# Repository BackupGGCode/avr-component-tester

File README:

The firmware was specificly designed to on an Atmega328p but really; 
any 28pin atmega 8k and up will work; and as long as your utilizing 
winavr just make sure you include its IO header file; you should be 
able to upload the source no problem. Ensure to double check the 
pinout and make changes as needed.

At some point I will most likly include differnt pre-compiled files 
for multiple atmega's for the public, depending on if there is any 
demand at all. Most likly there will be none, as its really just a 
personal project.

I also have some left-over PCBs; so if your interested just contact
BrentBXR and I might be able to mail you one. As long as you promise 
to build it up, and enjoy it. I wont send somone a PCB just so they 
can have a PCB laying around...

Thanks -BrentBXR [@gmail]

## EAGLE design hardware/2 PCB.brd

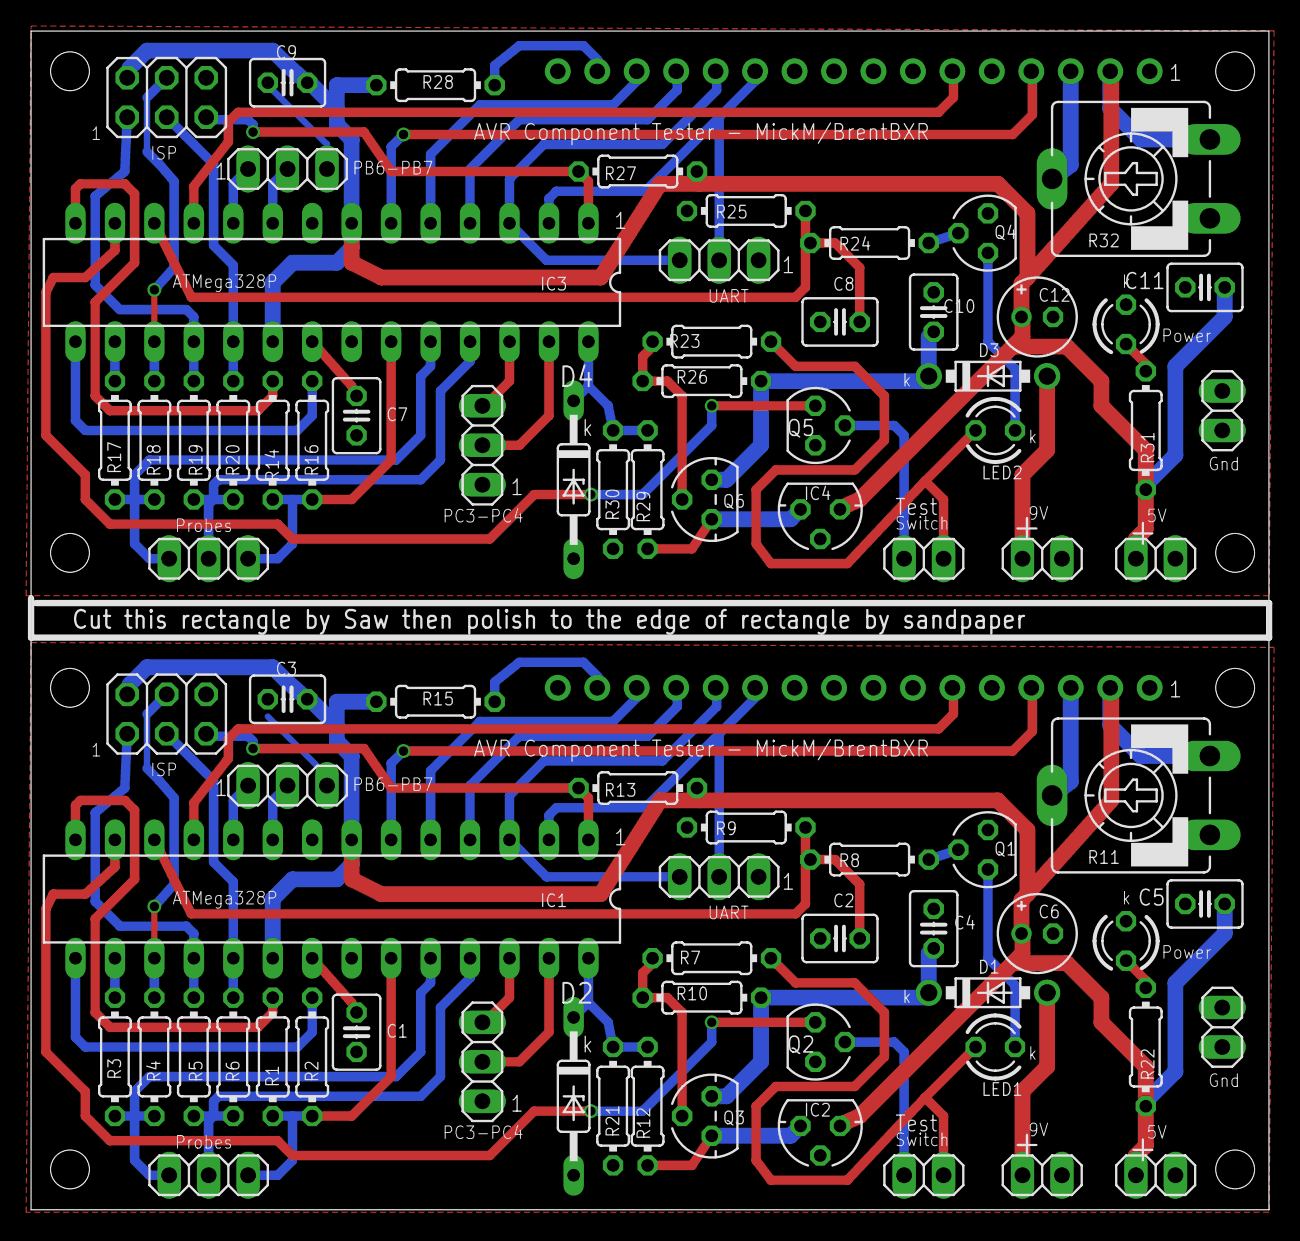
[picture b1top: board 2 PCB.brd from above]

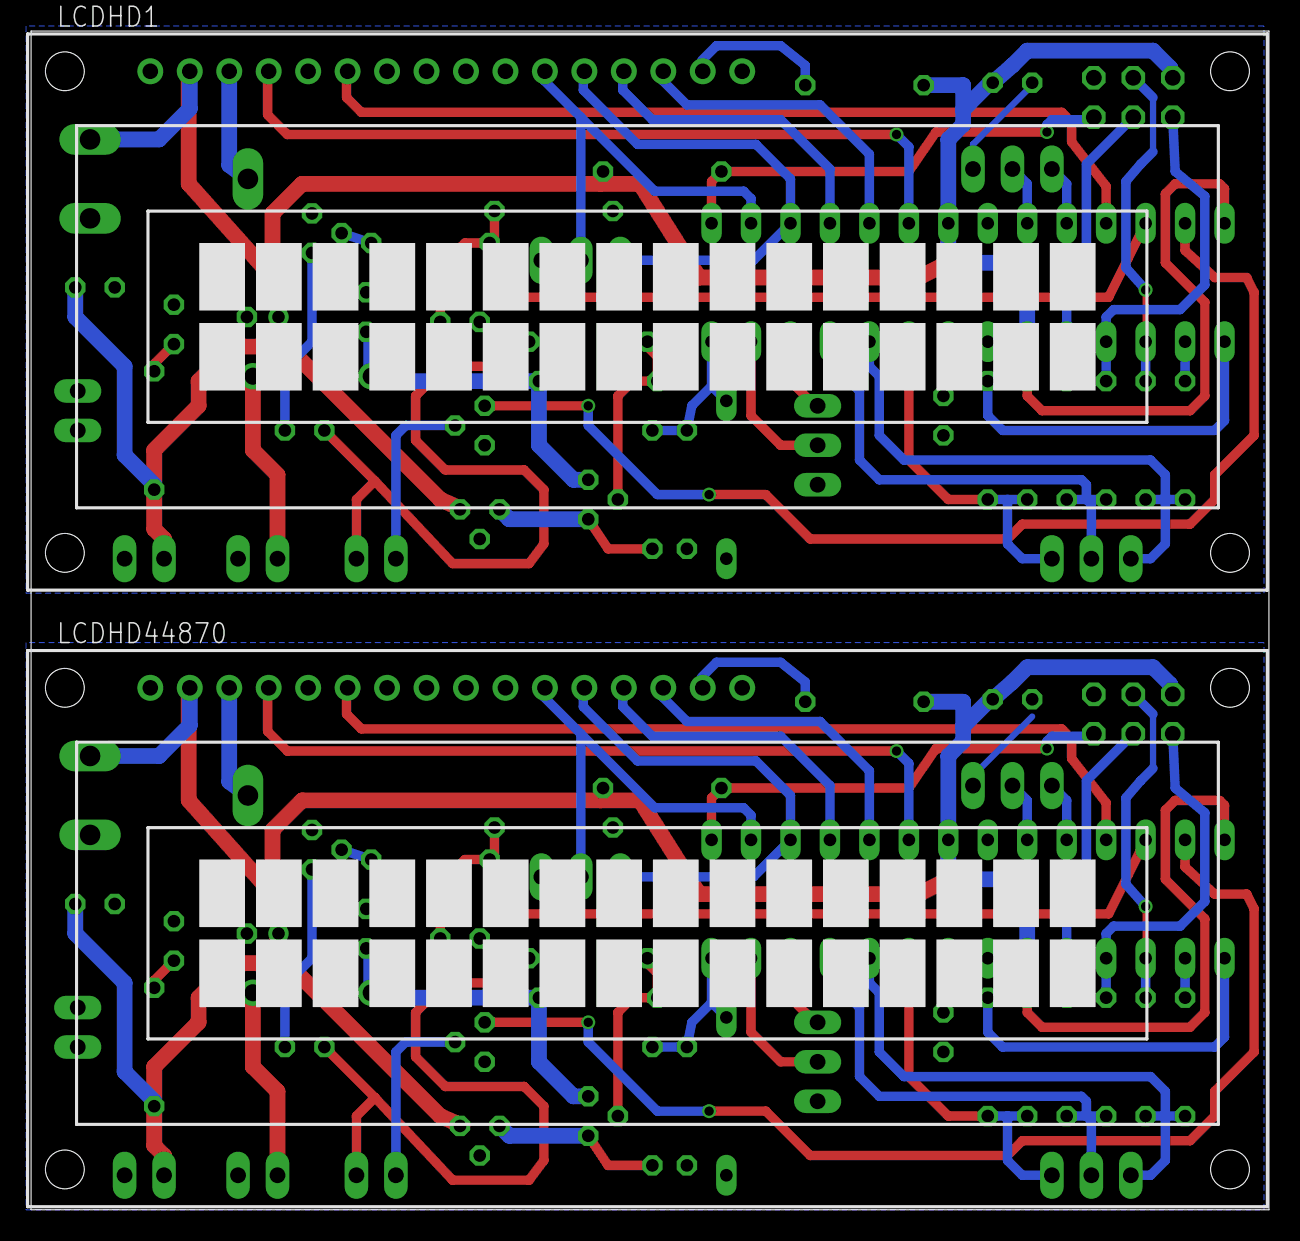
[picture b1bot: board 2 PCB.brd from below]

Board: 2 copper layers, 79.7 x 75.9 mm, 82 parts (2 on the bottom side), 74 nets.

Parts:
9V-DC-IN, 9V-DC-IN1: 1X02
C1, C3, C4, C5, C7, C9, C10, C11: 100n; C025-030X050
C2, C8: 100nF; C025-030X050
C6, C12: 100uF; E2-5
D1, D3: 1N5817-B; DO41-7.6
D2, D4: 5V1; DO35Z10
GND, GND1: 1X02
IC1, IC3: MEGA8-P; DIL28-3
IC2, IC4: 7805L; 78LXX
ISP, ISP1: 2X03
LCDHD1, LCDHD44870: TUXGR_16X2_R2
LED1, LED2: LED; LED3MM
PB6-PB1, PB6-PB7: 1X03
PC3-PC1, PC3-PC4: 1X03
PROBES, PROBES1: 1X03
PWR, PWR1: LED; LED3MM
Q1, Q2, Q4, Q5: BC547; SOT54A
Q3, Q6: BC557; TO92
R1, R3, R5, R14, R17, R19: 750R; 0204/7
R2, R4, R6, R16, R18, R20: 500K; 0204/7
R7, R23: 27k; 0204/7
R8, R24: 27K; 0204/7
R9, R25: 100K; 0204/7
R10, R26: 33K; 0204/7
R11, R32: 10K; CA9V
R12, R13, R27, R29: 10K; 0204/7
R15, R28: 150R; 0204/7
R21, R30: 3K3; 0204/7
R22, R31: 680R; 0204/7
TEST-SWITCH, TEST-SWITCH1: 1X02
UART, UART1: 1X03
VCC-GND, VCC-GND1: 1X02

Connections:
+5V: C3.1, C5.1, C6.+, IC1.7, IC1.20, IC2.OUT, ISP.2, LCDHD44870.2, R11.E, R13.1, R15.2, R22.1, VCC-GND.1
+5V1: C9.1, C11.1, C12.+, IC3.7, IC3.20, IC4.OUT, ISP1.2, LCDHD1.2, R27.1, R28.2, R31.1, R32.E, VCC-GND1.1
BAT-MON: D2.C, IC1.28, R12.2, R21.1
BAT-MON1: D4.C, IC3.28, R29.2, R30.1
GND: 9V-DC-IN.2, C1.2, C2.2, C3.2, C4.2, C5.2, C6.-, D2.A, GND.1, GND.2, IC1.8, IC1.22, IC2.GND, ISP.6, LCDHD44870.1, LCDHD44870.5, LCDHD44870.16, PB6-PB7.3, PC3-PC4.1, PWR.K, Q1.E, Q2.E, R9.1, R11.A, R21.2, UART.1, VCC-GND.2
GND1: 9V-DC-IN1.2, C7.2, C8.2, C9.2, C10.2, C11.2, C12.-, D4.A, GND1.1, GND1.2, IC3.8, IC3.22, IC4.GND, ISP1.6, LCDHD1.1, LCDHD1.5, LCDHD1.16, PB6-PB1.3, PC3-PC1.1, PWR1.K, Q4.E, Q5.E, R25.1, R30.2, R32.A, UART1.1, VCC-GND1.2
MISO: IC1.18, ISP.1, R5.1
MISO1: IC3.18, ISP1.1, R19.1
MOSI: IC1.17, ISP.4, R4.1
MOSI1: IC3.17, ISP1.4, R18.1
unnamed: IC2.IN, Q3.3, R12.1
unnamed: 9V-DC-IN.1, D1.A
unnamed: IC1.23, PROBES.3, R1.2, R2.2
unnamed: IC1.13, Q2.C
unnamed: IC1.25, PROBES.2, R5.2, R6.2
unnamed: IC1.14, R1.1
unnamed: IC1.15, R2.1
unnamed: IC1.16, R3.1
unnamed: PWR.A, R22.2
unnamed: IC3.23, PROBES1.3, R14.2, R16.2
unnamed: IC3.14, R14.1
unnamed: Q3.2, R7.2, R10.1
unnamed: IC1.6, LCDHD44870.4
unnamed: IC3.15, R16.1
unnamed: IC1.24, PROBES.1, R3.2, R4.2
unnamed: Q1.B, R8.2
unnamed: IC3.16, R17.1
unnamed: IC3.24, PROBES1.1, R17.2, R18.2
unnamed: IC1.9, PB6-PB7.2
unnamed: LED1.A, R7.1, TEST-SWITCH.2
unnamed: LED1.K, Q1.C
unnamed: Q2.B, TEST-SWITCH.1
unnamed: C2.1, IC1.12, R8.1, R9.2
unnamed: IC1.11, LCDHD44870.6
unnamed: Q6.2, R23.2, R26.1
unnamed: IC1.4, LCDHD44870.13
unnamed: IC1.5, LCDHD44870.14
unnamed: LCDHD44870.3, R11.S
unnamed: C1.1, IC1.21
unnamed: IC1.10, PB6-PB7.1
unnamed: LCDHD44870.15, R15.1
unnamed: Q4.B, R24.2
unnamed: C4.1, D1.C, Q3.1, R10.2
unnamed: IC1.26, PC3-PC4.3
unnamed: LED2.A, R23.1, TEST-SWITCH1.2
unnamed: LED2.K, Q4.C
unnamed: IC1.27, PC3-PC4.2
unnamed: Q5.B, TEST-SWITCH1.1
unnamed: IC3.6, LCDHD1.4
unnamed: IC3.4, LCDHD1.13
unnamed: IC3.5, LCDHD1.14
unnamed: IC3.11, LCDHD1.6
unnamed: LCDHD1.15, R28.1
unnamed: C10.1, D3.C, Q6.1, R26.2
unnamed: LCDHD1.3, R32.S
unnamed: 9V-DC-IN1.1, D3.A
unnamed: C7.1, IC3.21
unnamed: C8.1, IC3.12, R24.1, R25.2
unnamed: IC4.IN, Q6.3, R29.1
unnamed: IC3.26, PC3-PC1.3
unnamed: IC3.27, PC3-PC1.2
unnamed: IC3.9, PB6-PB1.2
unnamed: IC3.10, PB6-PB1.1
unnamed: IC3.25, PROBES1.2, R19.2, R20.2
unnamed: PWR1.A, R31.2
unnamed: IC3.13, Q5.C
RST: IC1.1, ISP.5, R13.2
RST1: IC3.1, ISP1.5, R27.2
RXD: IC1.2, LCDHD44870.11, UART.2
RXD1: IC3.2, LCDHD1.11, UART1.2
SCK: IC1.19, ISP.3, R6.1
SCK1: IC3.19, ISP1.3, R20.1
TXD: IC1.3, LCDHD44870.12, UART.3
TXD1: IC3.3, LCDHD1.12, UART1.3

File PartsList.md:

&lt;BR&gt;

Edited partlist exported from Eagle


&lt;BR&gt;




&lt;BR&gt;




&lt;BR&gt;

9V-DC-IN                     1X02


&lt;BR&gt;

GND                          1X02


&lt;BR&gt;

PB6-PB7                      1X03


&lt;BR&gt;

PC3-PC4                      1X03


&lt;BR&gt;

PROBES                       1X03


&lt;BR&gt;

TEST-SWITCH                  1X02


&lt;BR&gt;

UART                         1X03


&lt;BR&gt;

VCC-GND                      1X02          - 20 pins total


&lt;BR&gt;




&lt;BR&gt;

LCD    ------------------- 1X16          dont forget the LCD, male default, pcbs, back to back.


&lt;BR&gt;




&lt;BR&gt;

ISP                          2X03


&lt;BR&gt;




&lt;BR&gt;

C1          100n


&lt;BR&gt;

C2          100n


&lt;BR&gt;

C3          100n


&lt;BR&gt;

C4          100n


&lt;BR&gt;

C5          100n         5 total


&lt;BR&gt;




&lt;BR&gt;

C6          100uF


&lt;BR&gt;




&lt;BR&gt;

D1          1N5817-B


&lt;BR&gt;

D2          5V1


&lt;BR&gt;




&lt;BR&gt;

IC1         MEGA328-P


&lt;BR&gt;

IC2         7805L          v-reg  looks like a TO-92 transistor


&lt;BR&gt;




&lt;BR&gt;

LCDHD44870  16x02 Character LCD Display


&lt;BR&gt;




&lt;BR&gt;

LED1        LED         MUST NOT BE RED !!! Green is OK


&lt;BR&gt;

PWR         LED         Colour unimportant


&lt;BR&gt;




&lt;BR&gt;

Q1          BC547


&lt;BR&gt;

Q2          BC547


&lt;BR&gt;




&lt;BR&gt;

Q3          BC557


&lt;BR&gt;




&lt;BR&gt;

[R1](https://code.google.com/p/avr-component-tester/source/detail?r=1)          680R          NOTE: 1% or better tolerance.


&lt;BR&gt;

[R3](https://code.google.com/p/avr-component-tester/source/detail?r=3)          680R          NOTE: 1% or better tolerance.


&lt;BR&gt;

[R5](https://code.google.com/p/avr-component-tester/source/detail?r=5)          680R          NOTE: 1% or better tolerance. 3 total


&lt;BR&gt;




&lt;BR&gt;

[R2](https://code.google.com/p/avr-component-tester/source/detail?r=2)          470K          NOTE: 1% or better tolerance.


&lt;BR&gt;

[R4](https://code.google.com/p/avr-component-tester/source/detail?r=4)          470K          NOTE: 1% or better tolerance.


&lt;BR&gt;

[R6](https://code.google.com/p/avr-component-tester/source/detail?r=6)          470K          NOTE: 1% or better tolerance. 3 total
> 

&lt;BR&gt;




&lt;BR&gt;





&lt;BR&gt;

**All Below are 5% 1/4 W carbon**


&lt;BR&gt;




&lt;BR&gt;

[R7](https://code.google.com/p/avr-component-tester/source/detail?r=7)          27k


&lt;BR&gt;

[R8](https://code.google.com/p/avr-component-tester/source/detail?r=8)          27K           2 total


&lt;BR&gt;




&lt;BR&gt;

[R9](https://code.google.com/p/avr-component-tester/source/detail?r=9)          100K


&lt;BR&gt;




&lt;BR&gt;

[R10](https://code.google.com/p/avr-component-tester/source/detail?r=10)         33K


&lt;BR&gt;




&lt;BR&gt;

[R11](https://code.google.com/p/avr-component-tester/source/detail?r=11)         10K


&lt;BR&gt;

[R12](https://code.google.com/p/avr-component-tester/source/detail?r=12)         10K


&lt;BR&gt;

[R13](https://code.google.com/p/avr-component-tester/source/detail?r=13)         10K            3 total


&lt;BR&gt;




&lt;BR&gt;

[R15](https://code.google.com/p/avr-component-tester/source/detail?r=15)         150R


&lt;BR&gt;




&lt;BR&gt;

[R21](https://code.google.com/p/avr-component-tester/source/detail?r=21)         3K3


&lt;BR&gt;




&lt;BR&gt;

[R22](https://code.google.com/p/avr-component-tester/source/detail?r=22)         680R


&lt;BR&gt;




&lt;BR&gt;

**-----------------------------------------------------------------------------------------**


&lt;BR&gt;

**Shopping List:**


&lt;BR&gt;



&lt;BR&gt;

Headers 1X36


&lt;BR&gt;

Headers 2x3


&lt;BR&gt;




&lt;BR&gt;

0.1uF x 5


&lt;BR&gt;




&lt;BR&gt;

100uF


&lt;BR&gt;

1N5817


&lt;BR&gt;

5V1 Zener


&lt;BR&gt;

Mega328P


&lt;BR&gt;

7805L


&lt;BR&gt;

16x02 LCD Display


&lt;BR&gt;

LED x 2 one must be Green


&lt;BR&gt;

BC547 X 2


&lt;BR&gt;

BC557


&lt;BR&gt;

680R 1% x 3


&lt;BR&gt;

470k 1% x 3


&lt;BR&gt;

27K x 2


&lt;BR&gt;

100K


&lt;BR&gt;

33K


&lt;BR&gt;

10K x 3


&lt;BR&gt;

150R


&lt;BR&gt;

3K3


&lt;BR&gt;

680R

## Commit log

2012-02-18 oops
2012-02-18 Upload first compilation
2012-02-18 erry-day im shuffelin...
2012-02-18 shuffalin shuffalin..
2012-02-18 Added the hardware files
2012-02-18 Updating the readme files.
2012-02-20 Created a WINAVR (PN) project file (ACT.pnproj)
2012-02-20 Updated main.c's strings
2012-03-02 Added partslist, board and schematic pdf's
2012-03-05 Fixed the probe resistors; they where backwards and wrong values.
2012-03-05 Deleted useless bat
2012-03-05 new makefile and updated firmware
2012-03-05 Firmware v1.0 built. And firmware upgrade.
2012-03-05 Moved defines into settings.h; updated the makefile to allow programming.
2012-03-05 Fix in the partslist
2012-03-05 Just added a neat little percentage shown during testing. Just for looks really but is also informational incase it gets stuck we can trace at what testing point it was stuck.
2012-03-06 Changes include: * Software UART has been removed. * lcd routines have been cleaned up and compacted * a testing percentage has been added for looks and function * the makefile has been re-developed 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
2012-03-06 Changes: * Major cleanup of settings.h * formatting main.c * created control defines (POWER_ON = turn on regulator, POWER_OFF, PWRMODE_SETUP, ...)
2012-03-07 Version 1.2 -Changes: * Fixed the messages for damaged or no parts found * Deleted useless EEPROM variables (only 30% used now) * Added two levels of percentage monitoring/stages: -> The Identifying 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
    BXR
2015-04-29 Migrating wiki contents from Google Code
